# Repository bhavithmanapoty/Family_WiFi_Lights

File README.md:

# Family_WiFi_Lights
NodeMCU Project to use wifi and contact my family members

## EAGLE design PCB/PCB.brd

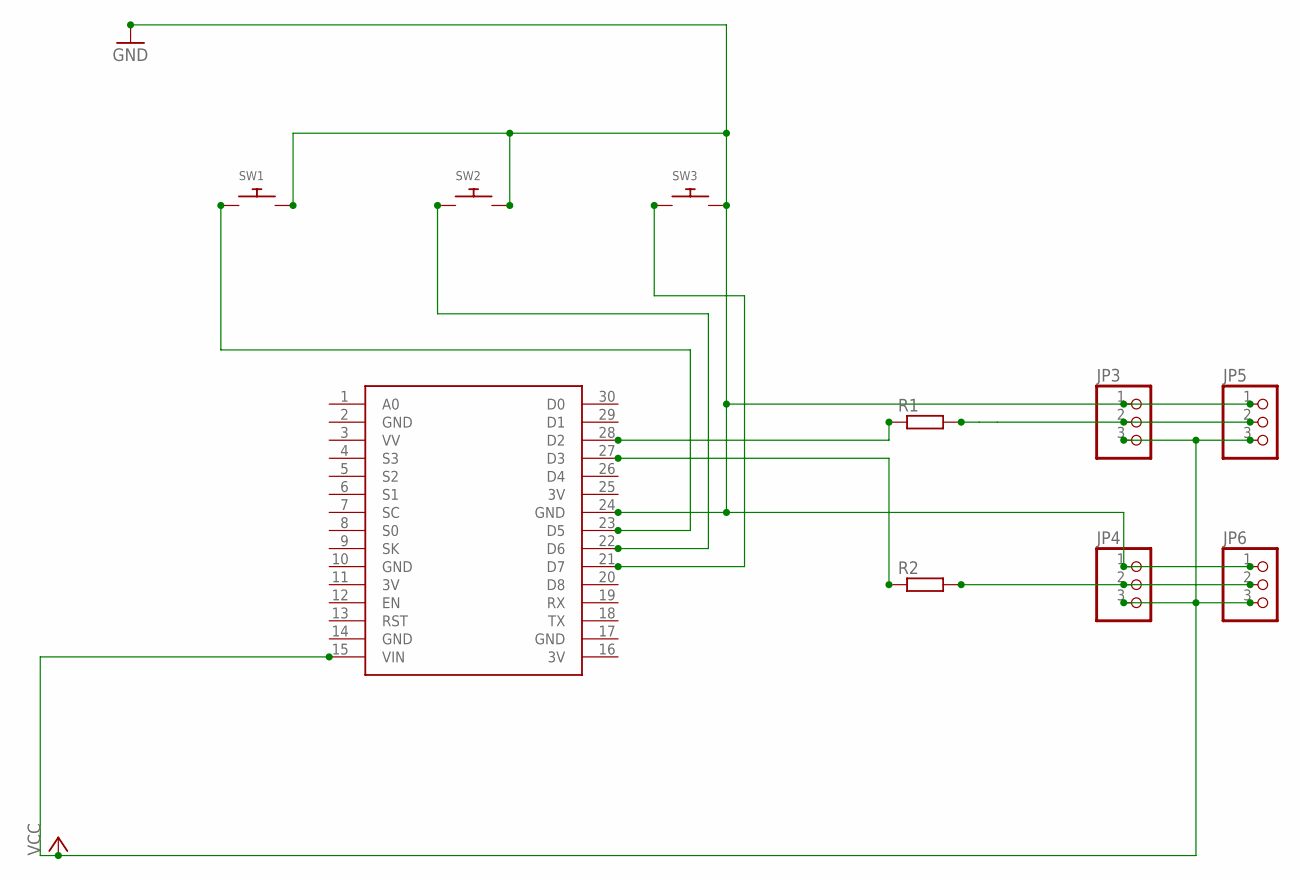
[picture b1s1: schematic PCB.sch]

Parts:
JP3, JP4, JP5, JP6: PINHD-1X3; 1X03
R1, R2: R-EU_0204/5; 0204/5
SW1, SW2, SW3: SWITCH_PUSHBUTTONEVQ-PE; TACT_PANA-EVQ
U$1: NODEMCU

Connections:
3V: U$1.11 (3V), U$1.16 (3V), U$1.25 (3V)
GND: JP3.1, JP4.1, JP5.1, JP6.1, SW1.P$2, SW2.P$2, SW3.P$2, U$1.2 (GND), U$1.10 (GND), U$1.14 (GND), U$1.17 (GND), U$1.24 (GND)
unnamed: SW1.P$1, U$1.23 (D5)
unnamed: SW2.P$1, U$1.22 (D6)
unnamed: R2.1, U$1.27 (D3)
unnamed: R1.1, U$1.28 (D2)
unnamed: SW3.P$1, U$1.21 (D7)
unnamed: JP4.2, JP6.2, R2.2
unnamed: JP3.2, JP5.2, R1.2
VCC: JP3.3, JP4.3, JP5.3, JP6.3, U$1.15 (VIN)

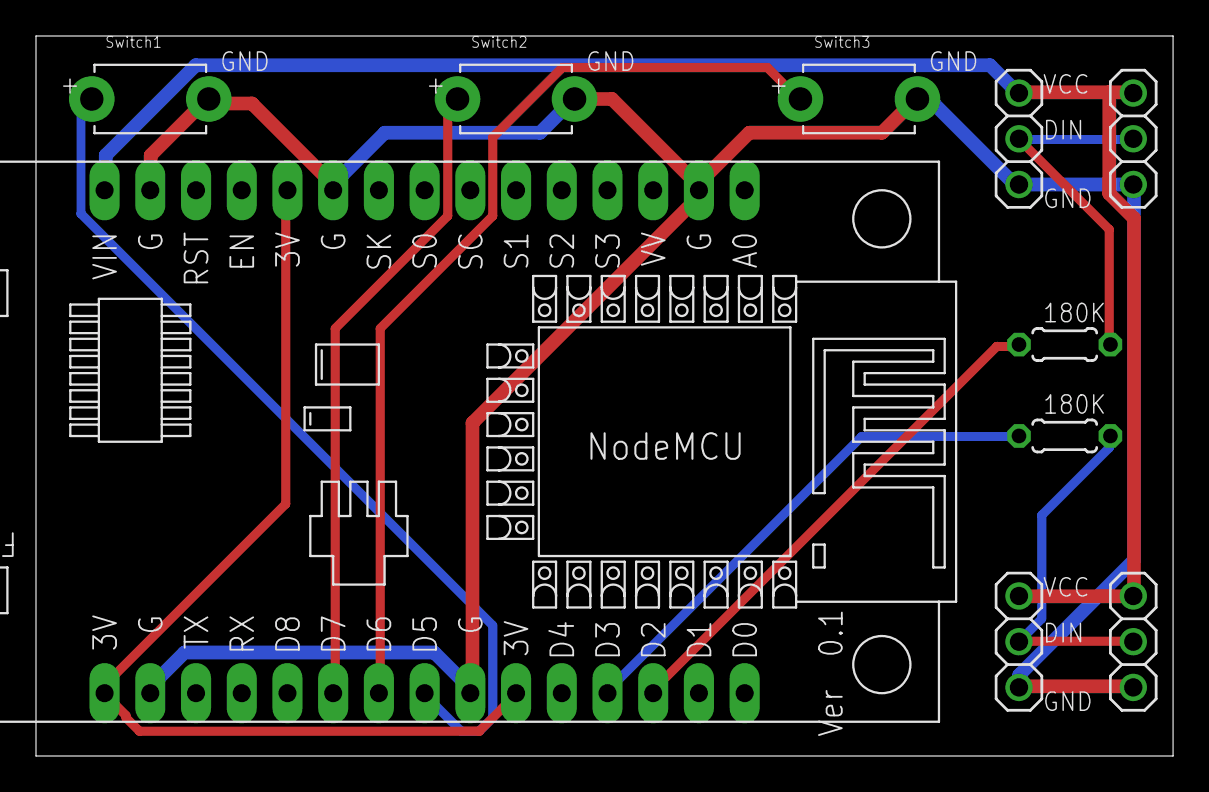
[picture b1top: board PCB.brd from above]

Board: 2 copper layers, 63.2 x 40.0 mm, 10 parts (0 on the bottom side), 10 nets.

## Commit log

2021-07-25 Moved design
2021-07-25 Added basic 3D Design
2021-07-25 Removed APIKey
2021-07-25 All basic codes completed
2021-07-25 Fixed debuggin bugs
2021-07-25 Removed API Keys
2021-08-01 Added LED Strip Compatibility
2021-08-03 Fixed all bugs
2021-08-03 Added PCB
2021-08-03 Added gerber
